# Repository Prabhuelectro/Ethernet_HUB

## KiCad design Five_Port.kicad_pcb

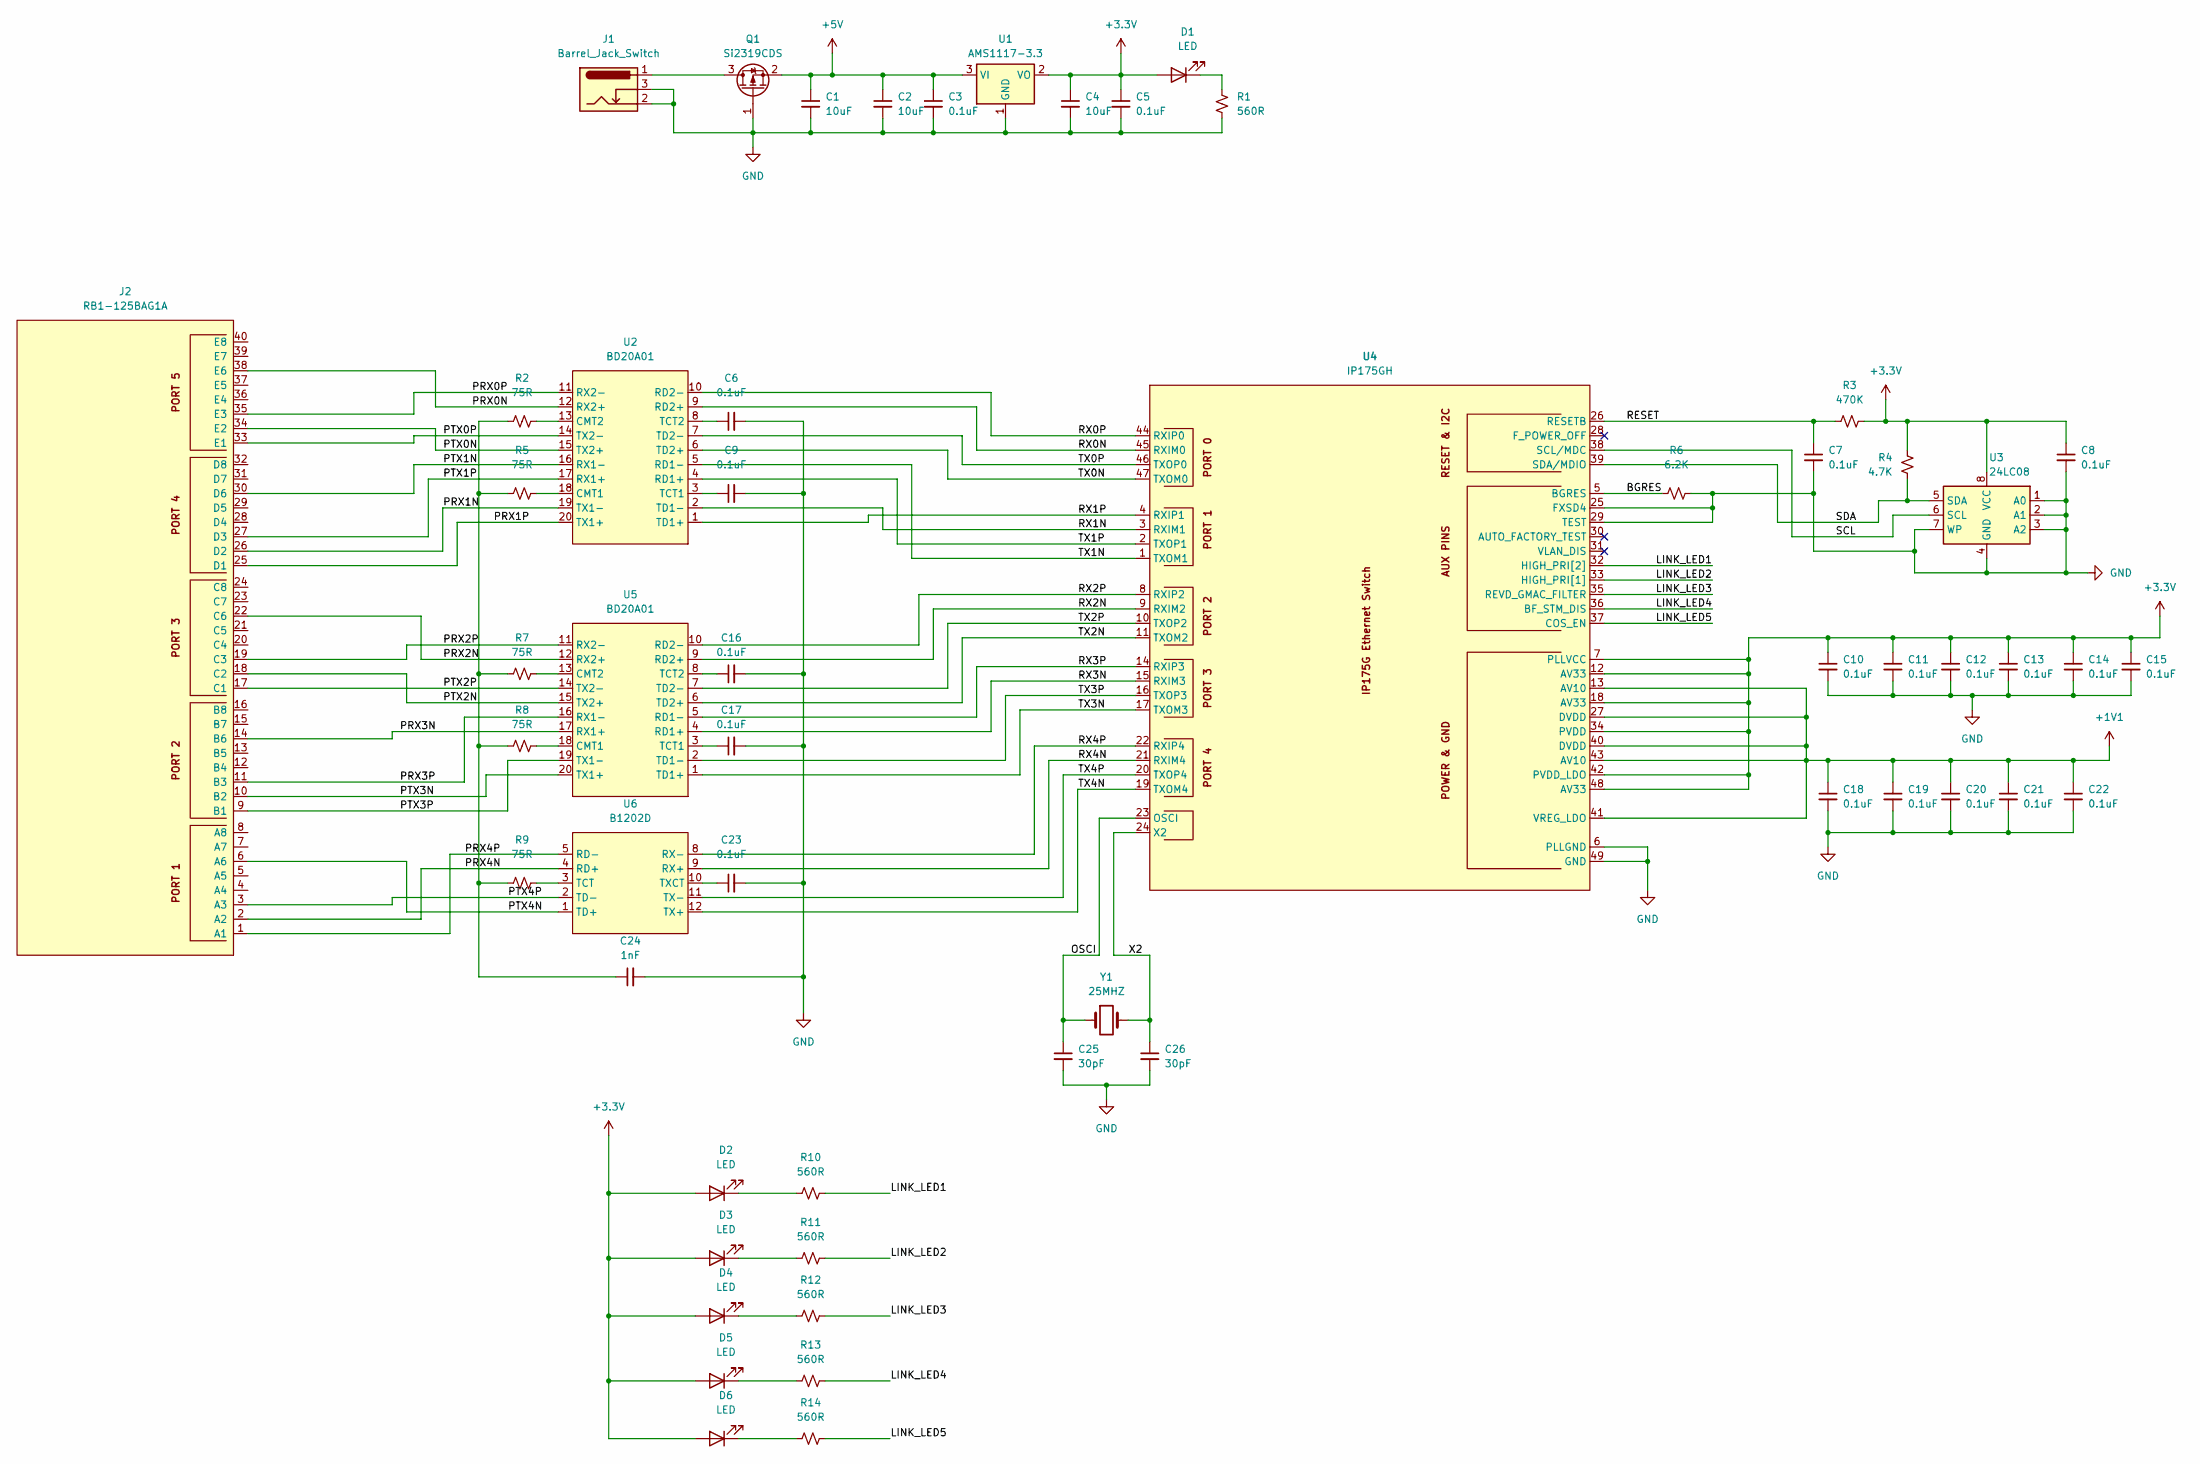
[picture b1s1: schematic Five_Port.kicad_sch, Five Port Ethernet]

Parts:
C1, C2: 10uF; C_0402_1005Metric
C3, C5, C6, C7, C8, C9, C10, C11, C12, C13, C14, C15, C16, C17, C18, C19, C20, C21, C22, C23: 0.1uF; C_0402_1005Metric
C4: 10uF; C_0603_1608Metric
C24: 1nF; C_1206_3216Metric
C25, C26: 30pF; C_0402_1005Metric
D1, D2, D3, D4, D5, D6: LED; LED_0603_1608Metric
J1: Barrel_Jack_Switch; BarrelJack_Wuerth_6941xx301002
J2: RB1-125BAG1A; ETH_5-Port_RC01459
Q1: Si2319CDS; SOT-23
R1: 560R; R_0402_1005Metric
R2, R5, R7, R8, R9: 75R; R_0402_1005Metric
R3: 470K; R_0402_1005Metric
R4: 4.7K; R_0402_1005Metric
R6: 6.2K; R_0402_1005Metric
R10, R11, R12, R13, R14: 560R; R_0603_1608Metric
U1: AMS1117-3.3; SOT-223-3_TabPin2
U2, U5: BD20A01
U3: 24LC08; SOIC-8_3.9x4.9mm_P1.27mm
U4: IP175GH; IP175GX
U6: B1202D
Y1: 25MHZ; Crystal_HC49-4H_Vertical

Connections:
+1V1: C18.1, C19.1, C20.1, C21.1, C22.1, U4.13 (AV10), U4.27 (DVDD), U4.40 (DVDD), U4.41 (VREG_LDO), U4.43 (AV10)
+3.3V: C4.1, C5.1, C8.1, C10.1, C11.1, C12.1, C13.1, C14.1, C15.1, D1.2 (A), D2.2 (A), D3.2 (A), D4.2 (A), D5.2 (A), D6.2 (A), R3.2, R4.2, U1.2 (VO), U3.8 (VCC), U4.7 (PLLVCC), U4.12 (AV33), U4.18 (AV33), U4.34 (PVDD), U4.42 (PVDD_LDO), U4.48 (AV33)
+5V: C1.1, C2.1, C3.1, Q1.2 (S), U1.3 (VI)
/BGRES: R6.1, U4.5 (BGRES)
/LINK_LED1: R10.2, U4.32 (HIGH_PRI[2])
/LINK_LED2: R11.2, U4.33 (HIGH_PRI[1])
/LINK_LED3: R12.2, U4.35 (REVD_GMAC_FILTER)
/LINK_LED4: R13.2, U4.36 (BF_STM_DIS)
/LINK_LED5: R14.2, U4.37 (COS_EN)
/OSCI: C25.1, U4.23 (OSCI), Y1.1
/PRX0N: J2.38 (E6), U2.12 (RX2+)
/PRX0P: J2.35 (E3), U2.11 (RX2-)
/PRX1N: J2.26 (D2), U2.19 (TX1-)
/PRX1P: J2.25 (D1), U2.20 (TX1+)
/PRX2N: J2.22 (C6), U5.12 (RX2+)
/PRX2P: J2.19 (C3), U5.11 (RX2-)
/PRX3N: J2.14 (B6), U5.17 (RX1+)
/PRX3P: J2.11 (B3), U5.16 (RX1-)
/PRX4N: J2.2 (A2), U6.4 (RD+)
/PRX4P: J2.1 (A1), U6.5 (RD-)
/PTX0N: J2.34 (E2), U2.15 (TX2+)
/PTX0P: J2.33 (E1), U2.14 (TX2-)
/PTX1N: J2.30 (D6), U2.16 (RX1-)
/PTX1P: J2.27 (D3), U2.17 (RX1+)
/PTX2N: J2.18 (C2), U5.15 (TX2+)
/PTX2P: J2.17 (C1), U5.14 (TX2-)
/PTX3N: J2.10 (B2), U5.20 (TX1+)
/PTX3P: J2.9 (B1), U5.19 (TX1-)
/PTX4N: J2.6 (A6), U6.1 (TD+)
/PTX4P: J2.3 (A3), U6.2 (TD-)
/RESET: C7.1, R3.1, U4.26 (RESETB)
/RX0N: U2.9 (RD2+), U4.45 (RXIM0)
/RX0P: U2.10 (RD2-), U4.44 (RXIP0)
/RX1N: U2.2 (TD1-), U4.3 (RXIM1)
/RX1P: U2.1 (TD1+), U4.4 (RXIP1)
/RX2N: U4.9 (RXIM2), U5.9 (RD2+)
/RX2P: U4.8 (RXIP2), U5.10 (RD2-)
/RX3N: U4.15 (RXIM3), U5.4 (RD1+)
/RX3P: U4.14 (RXIP3), U5.5 (RD1-)
/RX4N: U4.21 (RXIM4), U6.9 (RX+)
/RX4P: U4.22 (RXIP4), U6.8 (RX-)
/SCL: U3.6 (SCL), U4.38 (SCL/MDC)
/SDA: R4.1, U3.5 (SDA), U4.39 (SDA/MDIO)
/TX0N: U2.6 (TD2+), U4.47 (TXOM0)
/TX0P: U2.7 (TD2-), U4.46 (TXOP0)
/TX1N: U2.5 (RD1-), U4.1 (TXOM1)
/TX1P: U2.4 (RD1+), U4.2 (TXOP1)
/TX2N: U4.11 (TXOM2), U5.6 (TD2+)
/TX2P: U4.10 (TXOP2), U5.7 (TD2-)
/TX3N: U4.17 (TXOM3), U5.1 (TD1+)
/TX3P: U4.16 (TXOP3), U5.2 (TD1-)
/TX4N: U4.19 (TXOM4), U6.12 (TX+)
/TX4P: U4.20 (TXOP4), U6.11 (TX-)
/X2: C26.1, U4.24 (X2), Y1.2
GND: C1.2, C2.2, C3.2, C4.2, C5.2, C6.2, C7.2, C8.2, C9.2, C10.2, C11.2, C12.2, C13.2, C14.2, C15.2, C16.2, C17.2, C18.2, C19.2, C20.2, C21.2, C22.2, C23.2, C24.2, C25.2, C26.2, J1.2, J1.3, Q1.1 (G), R1.2, R6.2, U1.1 (GND), U3.1 (A0), U3.2 (A1), U3.3 (A2), U3.4 (GND), U3.7 (WP), U4.6 (PLLGND), U4.25 (FXSD4), U4.29 (TEST), U4.49 (GND)
unnamed: C24.1, R2.1, R5.1, R7.1, R8.1, R9.1
unnamed: D1.1 (K), R1.1
unnamed: D2.1 (K), R10.1
unnamed: D3.1 (K), R11.1
unnamed: D4.1 (K), R12.1
unnamed: D5.1 (K), R13.1
unnamed: D6.1 (K), R14.1
unnamed: J1.1, Q1.3 (D)
unnamed: R5.2, U2.18 (CMT1)
unnamed: R2.2, U2.13 (CMT2)
unnamed: C9.1, U2.3 (TCT1)
unnamed: C6.1, U2.8 (TCT2)
unnamed: R8.2, U5.18 (CMT1)
unnamed: R7.2, U5.13 (CMT2)
unnamed: C17.1, U5.3 (TCT1)
unnamed: C16.1, U5.8 (TCT2)
unnamed: R9.2, U6.3 (TCT)
unnamed: C23.1, U6.10 (TXCT)

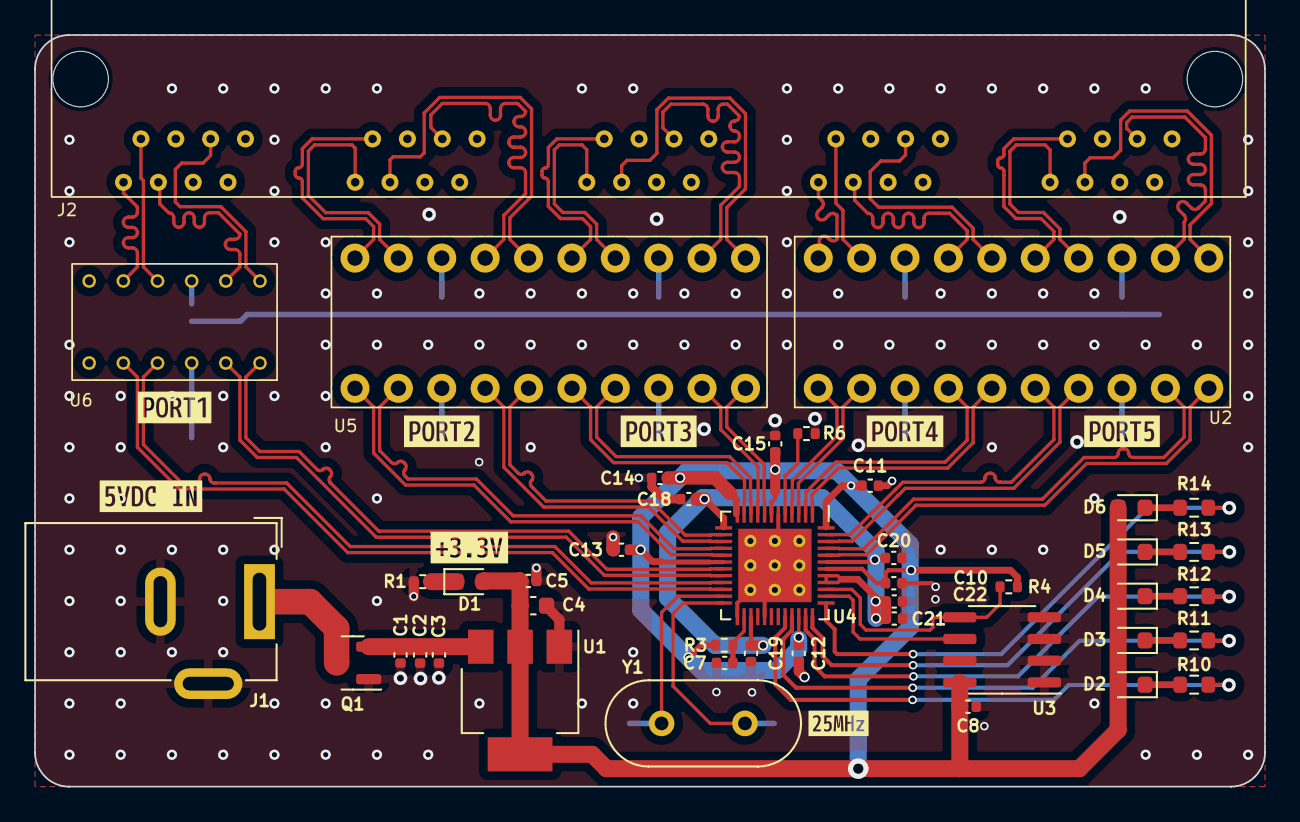
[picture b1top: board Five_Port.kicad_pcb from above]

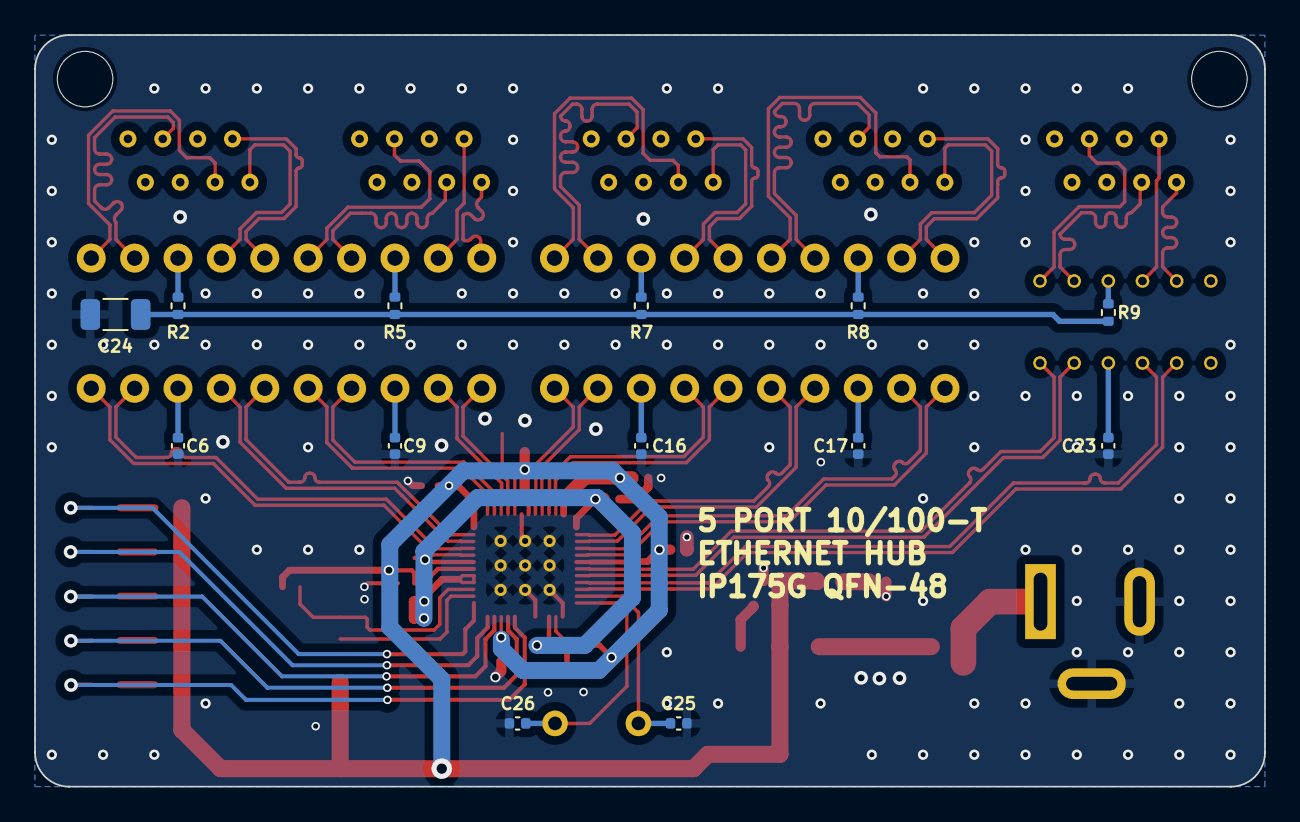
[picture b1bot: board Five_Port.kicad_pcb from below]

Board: 4 copper layers, 72.0 x 44.0 mm, 64 parts (13 on the bottom side), 73 nets.

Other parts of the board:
kibuzzard-653FC5D3: G***; kibuzzard-653FC5D3
kibuzzard-653FC5FE: G***; kibuzzard-653FC5FE
kibuzzard-653FC52A: G***; kibuzzard-653FC52A
kibuzzard-653FC56A: G***; kibuzzard-653FC56A
kibuzzard-653FC61D: G***; kibuzzard-653FC61D
kibuzzard-653FC613: G***; kibuzzard-653FC613
kibuzzard-653FC639: G***; kibuzzard-653FC639
kibuzzard-6540906E: G***; kibuzzard-6540906E

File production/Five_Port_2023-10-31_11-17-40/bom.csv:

Designator,Footprint,Quantity,Value,LCSC Part #
"C1, C2",0402,2,10uF,
"C10, C11, C12, C13, C14, C15, C16, C17, C18, C19, C20, C21, C22, C23, C3, C5, C6, C7, C8, C9",0402,20,0.1uF,
C24,1206,1,1nF,
"C25, C26",0402,2,30pF,
C4,0603,1,10uF,
"D1, D2, D3, D4, D5, D6",0603,6,LED,
J1,BarrelJack_Wuerth_6941xx301002,1,Barrel_Jack_Switch,
J2,ETH_5-Port_RC01459,1,RB1-125BAG1A,
Q1,SOT-23,1,Si2319CDS,
R1,0402,1,560R,
"R10, R11, R12, R13, R14",0603,5,560R,
"R2, R5, R7, R8, R9",0402,5,75R,
R3,0402,1,470K,
R4,0402,1,4.7K,
R6,0402,1,6.2K,
U1,SOT-223-3_TabPin2,1,AMS1117-3.3,
"U2, U5",BD20A01,2,BD20A01,
U3,SOIC-8_3.9x4.9mm_P1.27mm,1,24LC08,
U4,IP175GX,1,IP175GH,
U6,B1202D,1,B1202D,
Y1,Crystal_HC49-U_Vertical,1,25MHZ,

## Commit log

2024-03-15 100/10 Mbps Ethernet Five Port HUB
